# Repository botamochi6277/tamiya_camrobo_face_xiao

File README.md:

# TAMIYA CAMROBO FACE XIAO

An extension board for the face of [TAMIYA Cam-Program Robot](https://www.tamiya.com/english/products/70227/index.htm). 
This board has [Seeeduino XIAO](https://www.seeedstudio.com/Seeeduino-XIAO-Arduino-Microcontroller-SAMD21-Cortex-M0+-p-4426.html), RGB LEDs and a piezo speaker. 

- LED: Neopixel, [WS2812B](http://akizukidenshi.com/catalog/g/gI-07915/)
- Speaker: [muRata SMD piezo Speaker](http://akizukidenshi.com/catalog/g/gP-05723/)

LICENCE: [Open Source Hardware](https://www.oshwa.org/definition/)

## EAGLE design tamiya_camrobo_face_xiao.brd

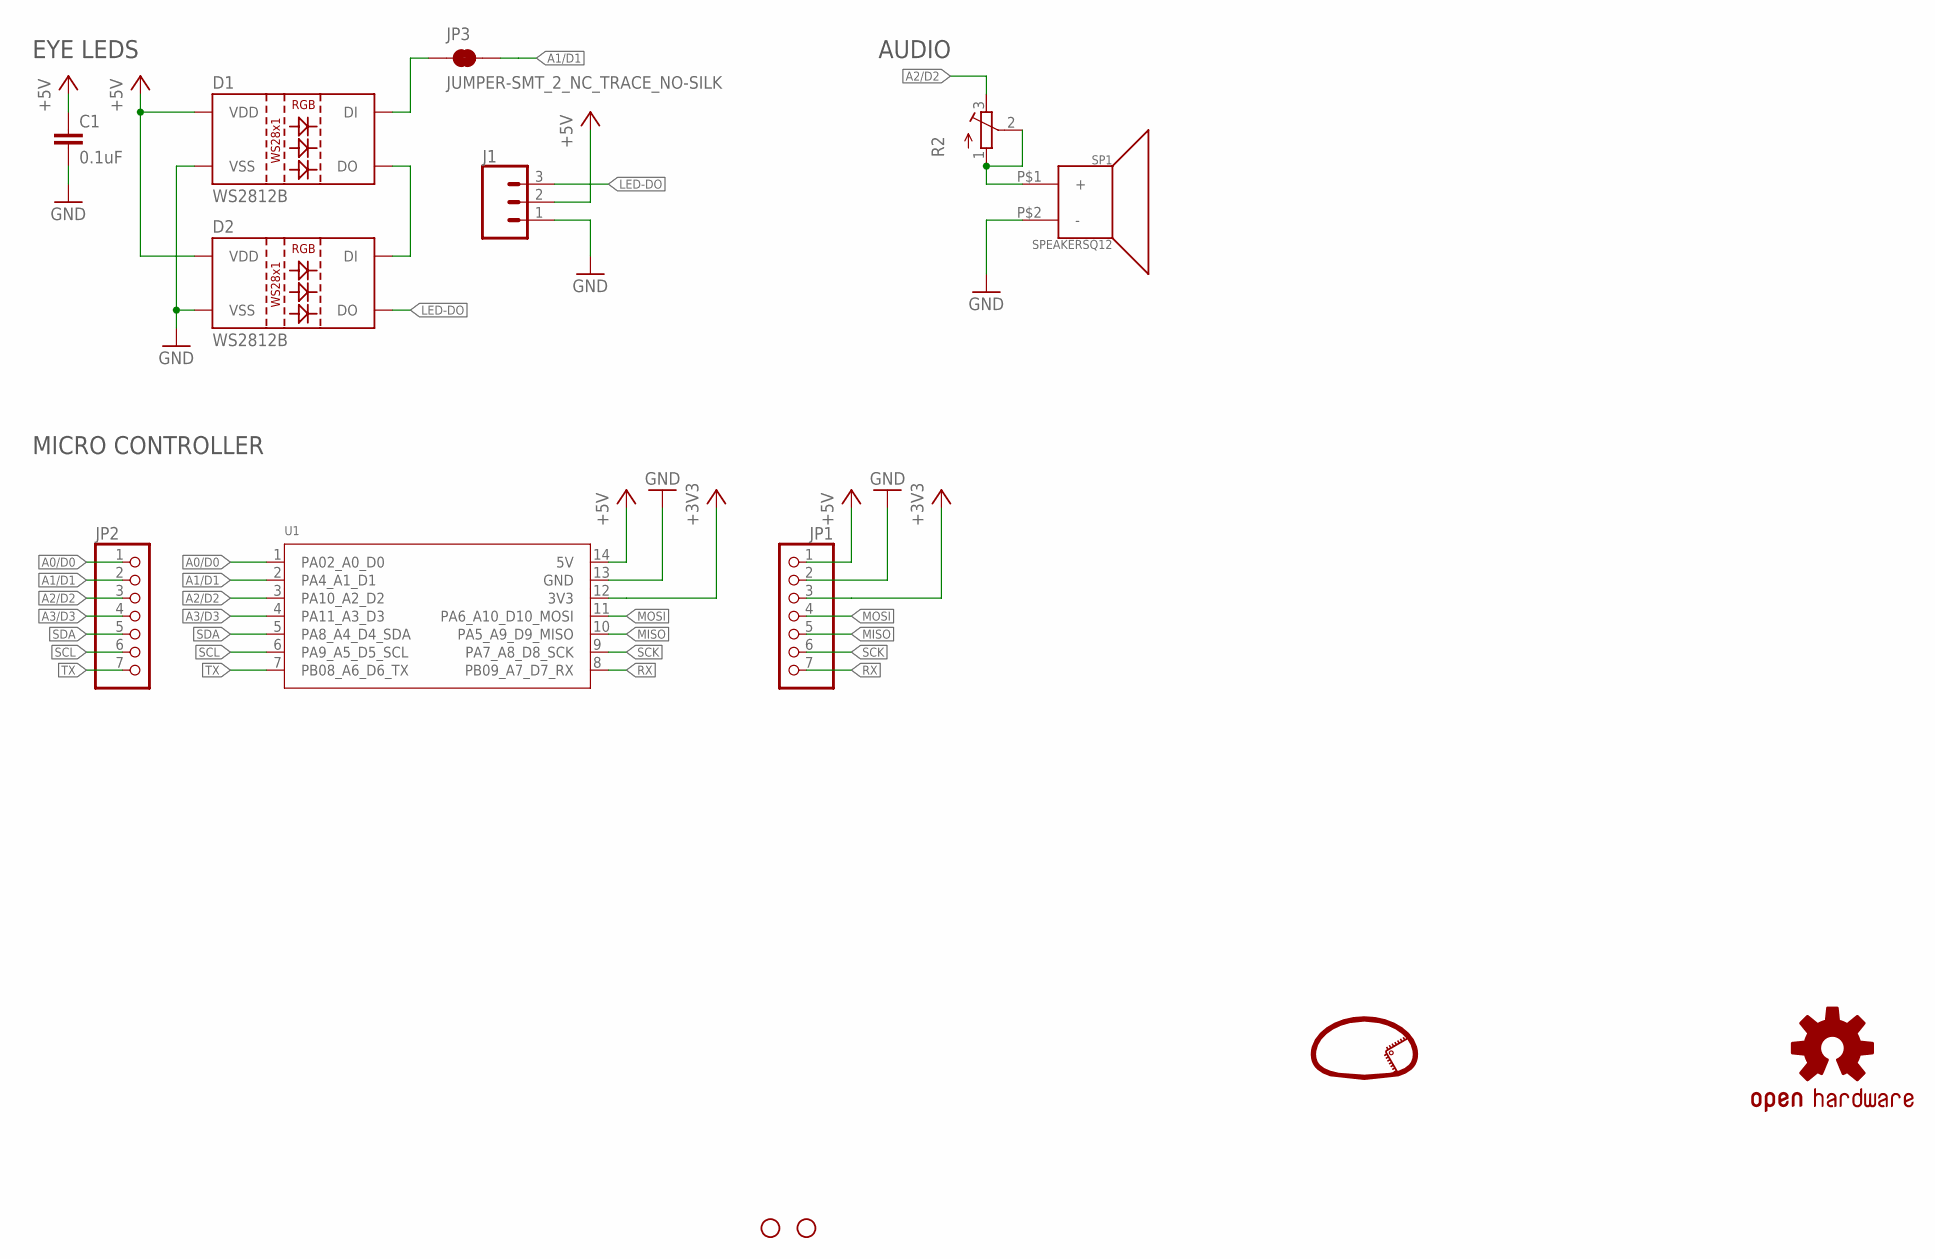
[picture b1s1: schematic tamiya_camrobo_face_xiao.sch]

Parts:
C1: 0.1uF; C1608
D1, D2: WS2812B
H1, H2: STAND-OFF
J1: CONN_03; 1X03
JP1, JP2: PINHD-1X7; 1X07
JP3: JUMPER-SMT_2_NC_TRACE_NO-SILK; SMT-JUMPER_2_NC_TRACE_NO-SILK
LOGO1: LOGO
LOGO2: OSHW-LOGOS; OSHW-LOGO-S
R2: R-TRIMMCVR42A; RTRIMCVR42A
SP1: SPEAKERSQ12; PKLCS1212E
U1: MOUDLE-SEEEDUINO-XIAO-MOUNTED; MOUDLE14P-2.54-21X17.8MM-MODIFIED

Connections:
+3V3: JP1.3, U1.12 (3V3)
+5V: C1.1, D1.1 (VDD), D2.1 (VDD), J1.2, JP1.1, U1.14 (5V)
A0/D0: JP2.1, U1.1 (PA02_A0_D0)
A1/D1: JP2.2, JP3.2, U1.2 (PA4_A1_D1)
A2/D2: JP2.3, R2.3 (E), U1.3 (PA10_A2_D2)
A3/D3: JP2.4, U1.4 (PA11_A3_D3)
GND: C1.2, D1.3 (VSS), D2.3 (VSS), J1.1, JP1.2, SP1.P$2 (-), U1.13 (GND)
LED-DO: D2.2 (DO), J1.3
MISO: JP1.5, U1.10 (PA5_A9_D9_MISO)
MOSI: JP1.4, U1.11 (PA6_A10_D10_MOSI)
unnamed: D1.2 (DO), D2.4 (DI)
unnamed: R2.1 (A), R2.2 (S), SP1.P$1 (+)
unnamed: D1.4 (DI), JP3.1
RX: JP1.7, U1.8 (PB09_A7_D7_RX)
SCK: JP1.6, U1.9 (PA7_A8_D8_SCK)
SCL: JP2.6, U1.6 (PA9_A5_D5_SCL)
SDA: JP2.5, U1.5 (PA8_A4_D4_SDA)
TX: JP2.7, U1.7 (PB08_A6_D6_TX)

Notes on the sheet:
EYE LEDS
AUDIO
MICRO CONTROLLER

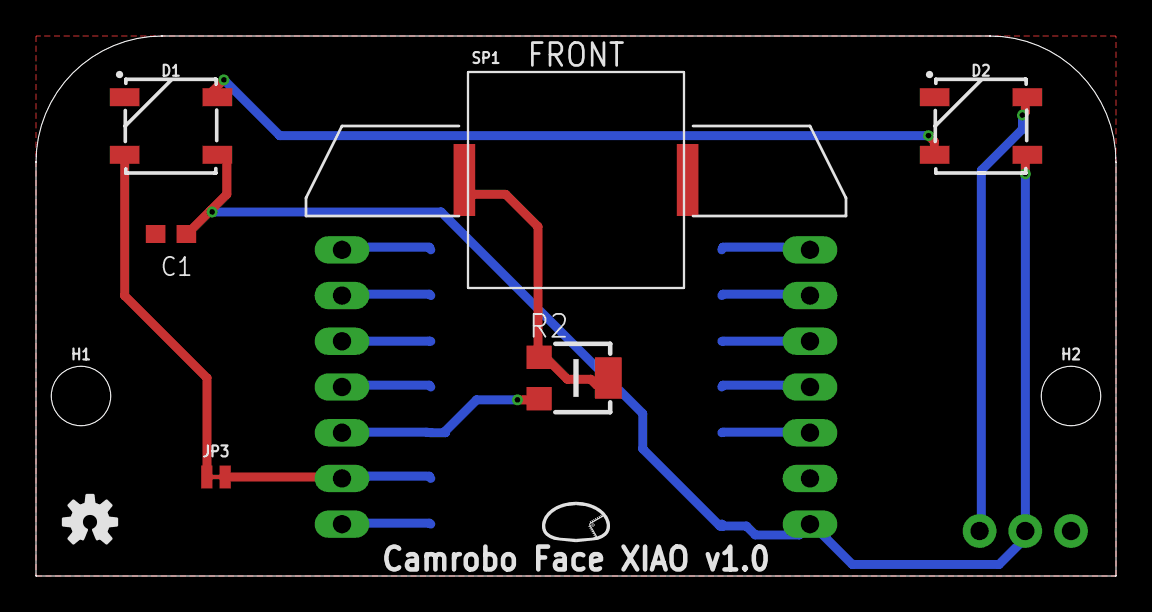
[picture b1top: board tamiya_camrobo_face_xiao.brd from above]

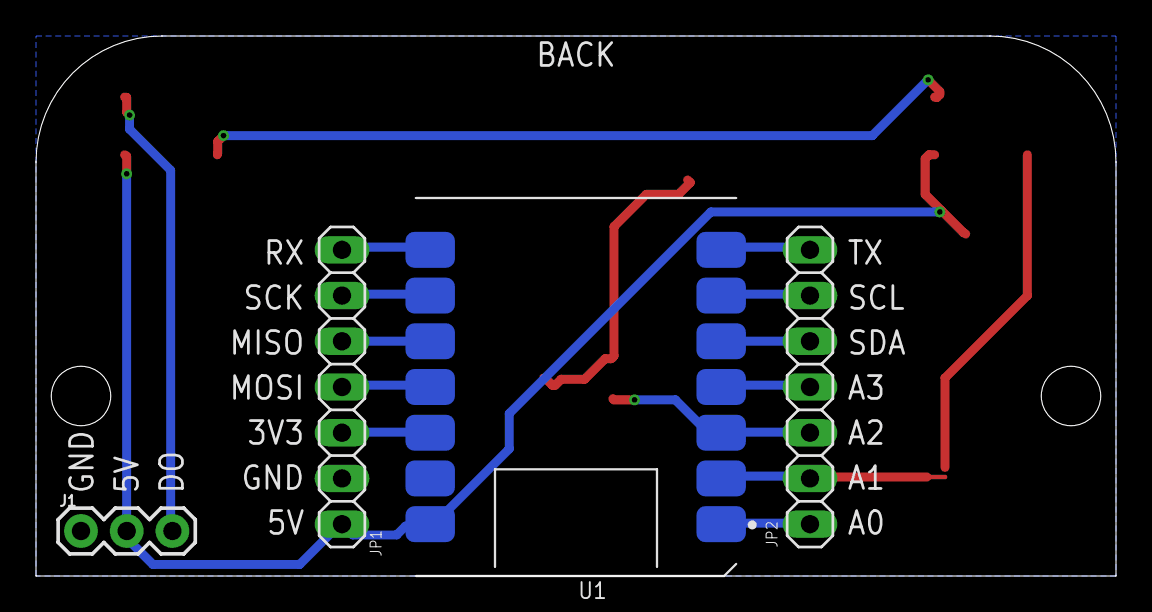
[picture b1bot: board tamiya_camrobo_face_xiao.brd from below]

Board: 2 copper layers, 60.0 x 30.0 mm, 14 parts (4 on the bottom side), 18 nets.

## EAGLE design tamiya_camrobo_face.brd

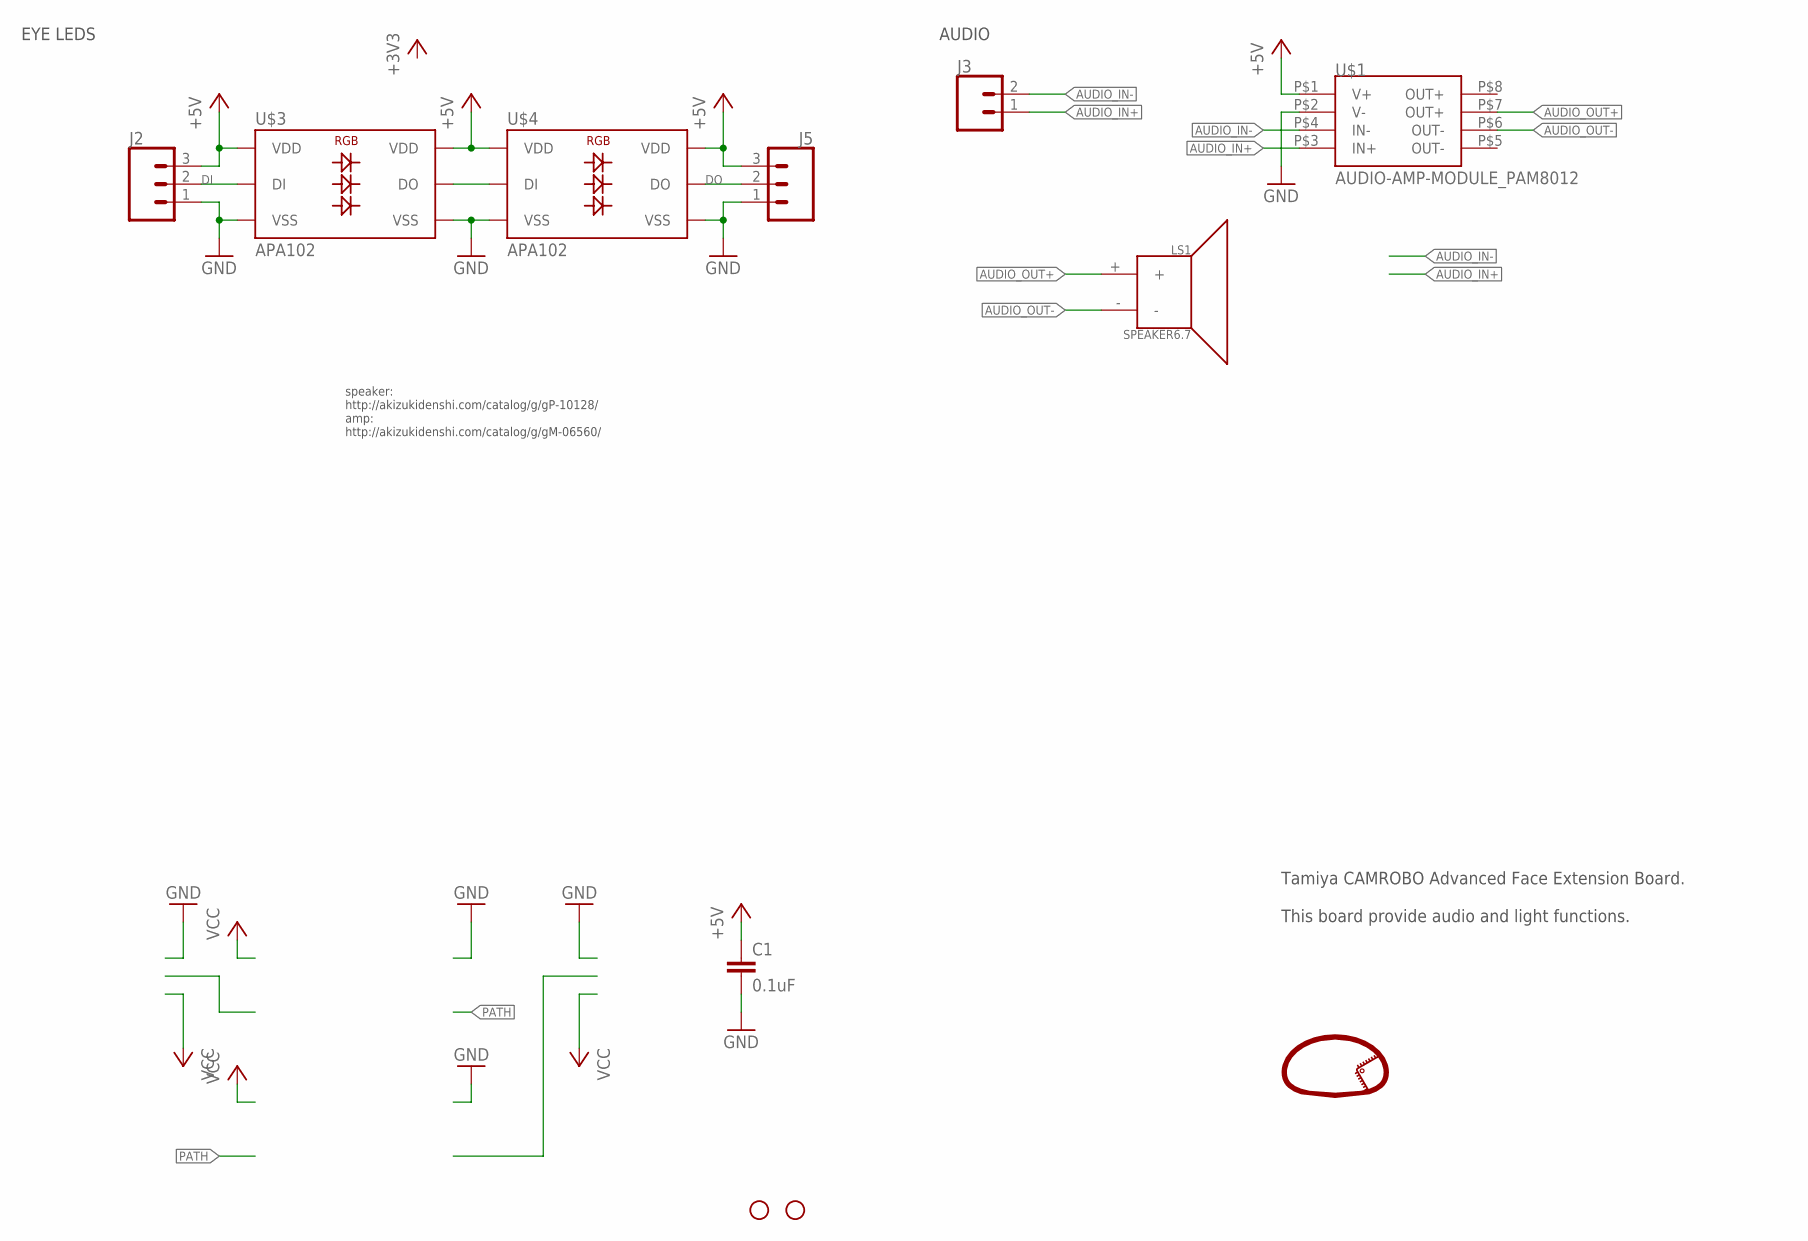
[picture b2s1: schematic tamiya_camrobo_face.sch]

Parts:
C1: 0.1uF; CAP-PTH-SMALL-KIT
H1, H2: STAND-OFF
J2, J5: CONN_03; 1X03
J3: CONN_02; 1X02
LS1: SPEAKER6.7; SPEAKER-6.7MM
U$1: AUDIO-AMP-MODULE_PAM8012; AE-PAM8012
U$2: LOGO
U$3, U$4: APA102; APA102-STRIP-ELEMENT

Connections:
+5V: C1.1, J2.3, J5.3, U$1.P$1 (V+), U$3.P$1 (VDD), U$3.P$6 (VDD), U$4.P$1 (VDD), U$4.P$6 (VDD)
AUDIO_IN+: J3.1, U$1.P$3 (IN+)
AUDIO_IN-: J3.2, U$1.P$4 (IN-)
AUDIO_OUT+: LS1.+, U$1.P$7 (OUT+)
AUDIO_OUT-: LS1.-, U$1.P$6 (OUT-)
DI: J2.2, U$3.P$5 (DI)
DO: J5.2, U$4.P$2 (DO)
GND: C1.2, J2.1, J5.1, U$1.P$2 (V-), U$3.P$3 (VSS), U$3.P$4 (VSS), U$4.P$3 (VSS), U$4.P$4 (VSS)
unnamed: U$3.P$2 (DO), U$4.P$5 (DI)

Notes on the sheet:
speaker: http://akizukidenshi.com/catalog/g/gP-10128/ amp: http://akizukidenshi.com/catalog/g/gM-06560/
Tamiya CAMROBO Advanced Face Extension Board. This board provide audio and light functions.
EYE LEDS
AUDIO

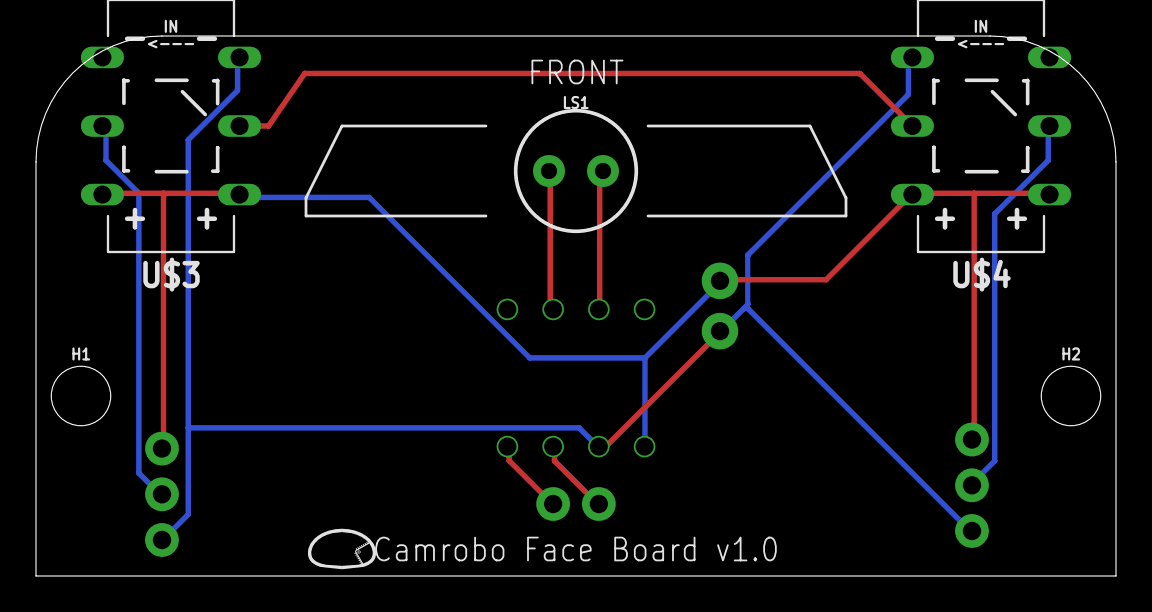
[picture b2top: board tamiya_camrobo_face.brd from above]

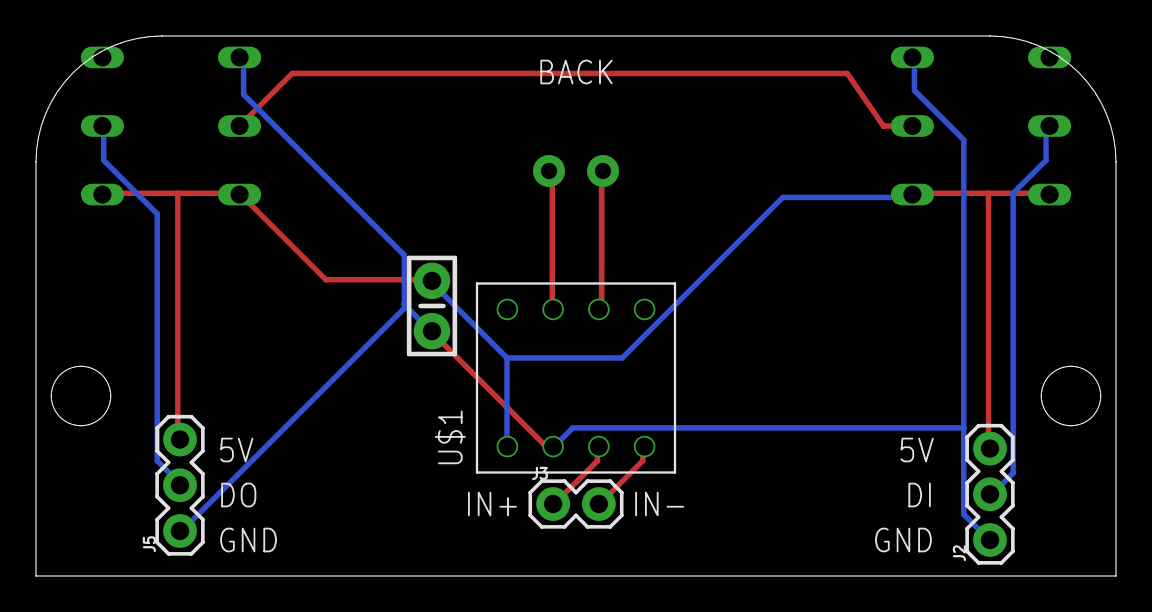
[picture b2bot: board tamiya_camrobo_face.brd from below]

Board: 2 copper layers, 60.0 x 30.0 mm, 11 parts (5 on the bottom side), 9 nets.

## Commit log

2020-02-18 exchange led and amp
2020-08-13 update read to xiao

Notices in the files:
parts and their libraries:
SparkFun-Capacitors: Licensing: Creative Commons ShareAlike 4.0 International - https://creativecommons.org/licenses/by-sa/4.0
